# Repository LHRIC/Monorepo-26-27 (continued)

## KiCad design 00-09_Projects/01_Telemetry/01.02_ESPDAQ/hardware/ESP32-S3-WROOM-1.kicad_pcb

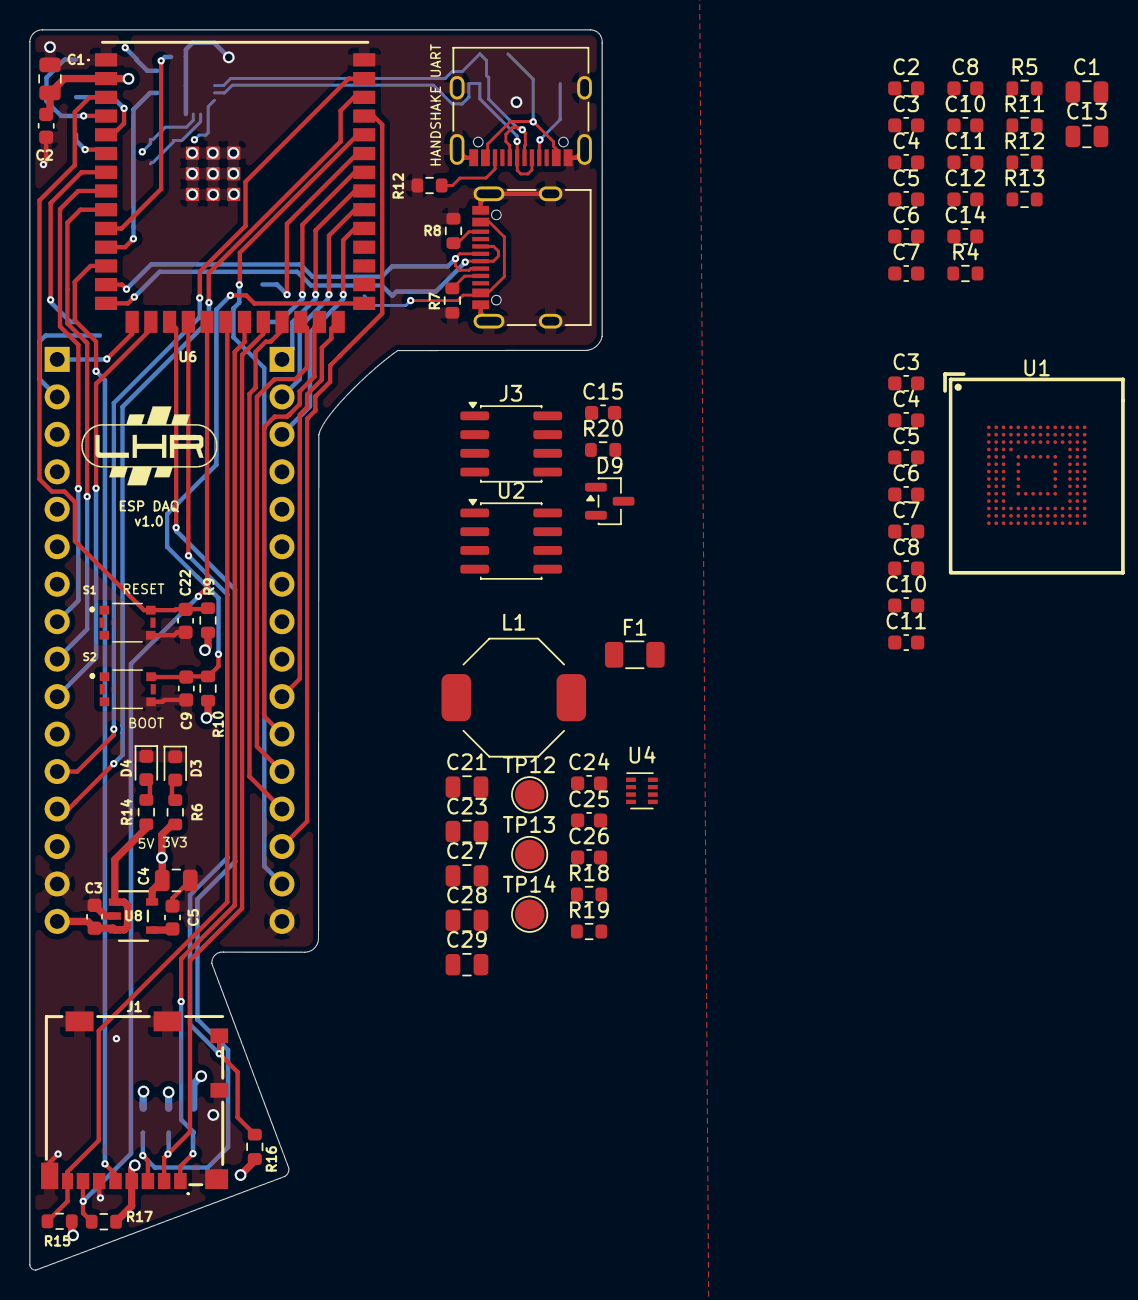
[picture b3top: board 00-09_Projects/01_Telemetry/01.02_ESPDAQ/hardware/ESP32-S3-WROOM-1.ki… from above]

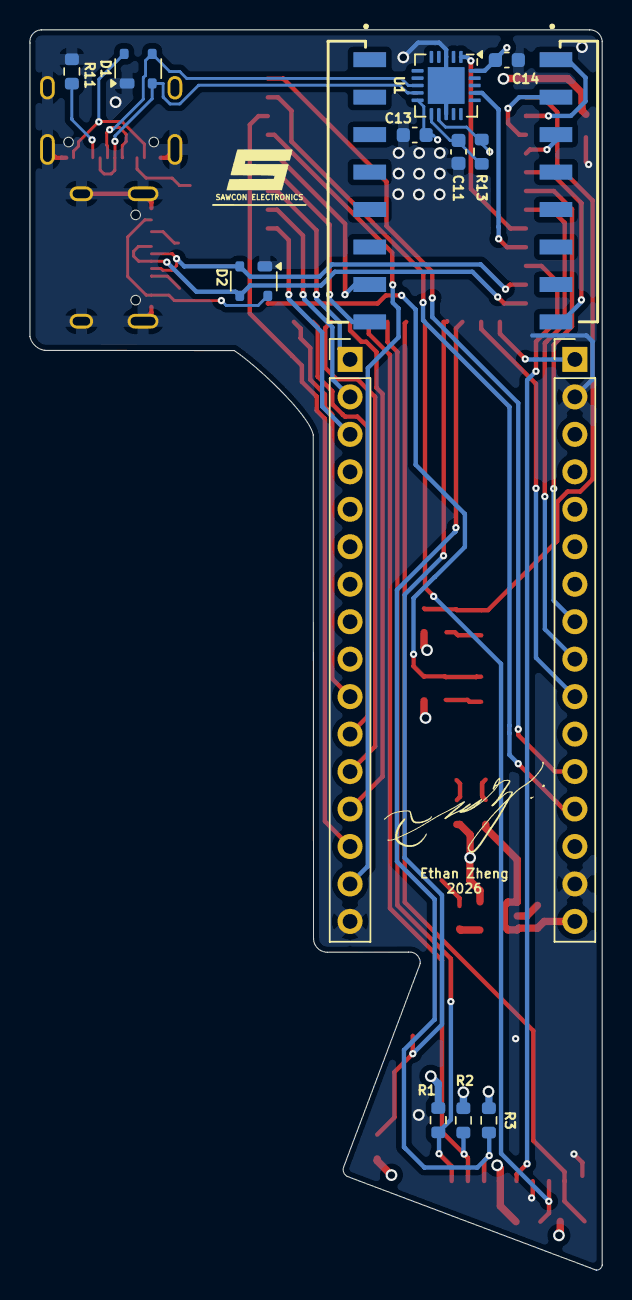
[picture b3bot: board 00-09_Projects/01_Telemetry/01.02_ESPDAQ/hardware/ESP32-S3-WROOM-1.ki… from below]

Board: 4 copper layers, 38.8 x 84.1 mm, 89 parts (15 on the bottom side), 42 nets.

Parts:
C1, C1#2, C13, C27, C28, C29: 22uF; C_0805_2012Metric
C2, C2#2, C3, C3#3, C4#2, C4#3, C5#2, C5#3, C6, C6#2, C7, C7#2, C8, C8#2, C9, C10, C10#2, C11, C11#2, C11#3, C12, C13#2, C14, C14#2, C15: 0.1uF; C_0603_1608Metric
C3#2: .47uF; C_0603_1608Metric
C4: 33uF; C_0805_2012Metric
C5: 100pF; C_0603_1608Metric
C21, C23: 4.7uF; C_0805_2012Metric
C22: 1uF; C_0603_1608Metric
C24, C26: .1uF; C_0603_1608Metric
C25: 33nF; C_0603_1608Metric
D1, D2: PRTR5V0U2X; SOT-143
D3, D4: RED; LED_0603_1608Metric
D9: D_TVS_Dual_AAC; SOT-23
F1: Fuse; Fuse_1206_3216Metric
J1: 104031-0811; Molex MicroSD Card 1040310811
J3: Conn_02x03_Counter_Clockwise; SOIC-8_3.9x4.9mm_P1.27mm
J9, J10: USB_C_Receptacle_USB2.0_14P; USB_C_Receptacle_XKB_U262-16XN-4BVC11
J12, J14: Conn_01x16; PinHeader_1x16_P2.54mm_Vertical
J15: Conn_01x08; 01x08 2.54mm Connector Surface Mount Right Angle Left
J16: Conn_01x08; 01x08 2.54mm Connector Surface Mount Right Angle Right
L1: 4.7uH; SRU8043-4R7Y
R1, R2, R3, R4, R5, R9, R10, R11, R12#2, R13, R15, R16, R17, R19: 10k; R_0603_1608Metric
R6, R14: 330; R_0603_1608Metric
R7, R8, R11#2, R12, R13#2: 5.1k; R_0603_1608Metric
R18: 30.9k; R_0603_1608Metric
R20: 120; R_0603_1608Metric
S1, S2: 435171014816; SMT Switch 435171014816
TP12, TP13, TP14: TP; TestPoint_Pad_D2.0mm
U1: KLMAG1JETD-B041; FBGA-153_L13.0-W11.5-P0.50_KLMAG1JETD-B041
U1#2: FT231XQ; QFN-20-1EP_4x4mm_P0.5mm_EP2.5x2.5mm
U2: SN65HVD230; SOIC-8_3.9x4.9mm_P1.27mm
U4: TPS62933; SOT-583
U6: ESP32-S3-WROOM-1; ESP32S3-WROOM-1U-N16R8
U8: AP2210K-3.3TRG1; SOT-23-5_DIO

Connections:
+3V3: C1.1, C1#2.1, C2.1, C2#2.1, C3.1, C3#3.1, C4.2, C4#2.1, C4#3.1, C5#2.1, C5#3.1, C6.1, C6#2.1, C7.1, C7#2.1, C8.1, C8#2.1, C10.1, C10#2.1, C11.1, C11#2.1, C12.1, C13.1, C13#2.1, C14.1, C14#2.2, C15.1, F1.2, J1.4 (VDD), R1.1, R2.1, R3.1, R4.1, R5.1, R6.1, R9.1, R10.1, R11.1, R12#2.1, R13.1, R13#2.2, R15.1, R16.1, R17.1, U1.C2 (VDDI), U1.C6 (VDD), U1.E6 (VDDF), U1.F5 (VDDF), U1.J10 (VDDF), U1.K9 (VDDF), U1.M4 (VDD), U1.N4 (VDD), U1.P3 (VDD), U1.P5 (VDD), U1#2.10 (3V3OUT), U1#2.12 (VCC), U1#2.20 (VCCIO), U2.3 (VCC), U6.2 (3V3), U8.5 (VOUT)
+5V: C3#2.2, C21.1, C23.1, C24.1, J3.1, J12.16, R14.1, TP12.1 (1_1), U4.3 (VIN), U8.1 (VIN), U8.3 (EN)
/BOOT: C9.2, R10.2, S2.2, U6.27 (IO0)
/RESET: C22.2, R9.2, S1.2, U6.3 (EN)
CAN_H: D9.2 (A2), J3.6, R20.1, U2.7 (CANH)
CAN_L: D9.1 (A1), J3.5, R20.2, U2.6 (CANL)
CAN_RX: J12.13, U2.4 (R), U6.38 (IO2)
CAN_TX: J12.12, U2.1 (D), U6.39 (IO1)
Data_Log: J3.4, J14.13, U6.23 (IO21)
GND: C1.2, C1#2.2, C2.2, C2#2.2, C3.2, C3#2.1, C3#3.2, C4.1, C4#2.2, C4#3.2, C5.1, C5#2.2, C5#3.2, C6.2, C6#2.2, C7.2, C7#2.2, C8.2, C8#2.2, C9.1, C10.2, C10#2.2, C11.2, C11#2.2, C11#3.2, C12.2, C13.2, C13#2.2, C14.2, C14#2.1, C15.2, C21.2, C22.1, C23.2, C24.2, C25.2, C27.2, C28.2, C29.2, D1.1 (GND), D2.1 (GND), D3.1 (K), D4.1 (K), D9.3 (common), J1.6 (VSS), J1.9, J1.10, J1.11, J1.13, J1.14, J3.3, J9.A1 (GND), J9.A12 (GND), J9.B1 (GND), J9.B12 (GND), J9.S1 (SHIELD), J10.A1 (GND), J10.A12 (GND), J10.B1 (GND), J10.B12 (GND), J10.S1 (SHIELD), J12.2, J12.15, J14.16, R7.2, R8.2, R11#2.2, R12.2, R19.2, S1.4, S1.6, S2.4, S2.6, TP13.1 (1_1), U1.A6 (VSS), U1.C4 (VSS), U1.E7 (VSS), U1.G5 (VSS), U1.H10 (VSS), U1.J5 (VSS), U1.K8 (VSS), U1.N2 (VSS), U1.N5 (VSS), U1.P4 (VSS), U1.P6 (VSS), U1#2.3 (GND), U1#2.13 (GND), U1#2.21 (GND), U2.2 (GND), U4.4 (GND), U6.1 (GND), U6.40 (GND), U6.41 (GND), U8.2 (GND)
MMC_CLK: U1.M6 (CLK), U6.35 (IO42)
MMC_CMD: R13.2, U1.M5 (CMD), U6.24 (IO47)
MMC_D0: R4.2, U1.A3 (DAT0), U6.31 (IO38)
MMC_D1: R5.2, U1.A4 (DAT1), U6.32 (IO39)
MMC_D2: R11.2, U1.A5 (DAT2), U6.33 (IO40)
MMC_D3: R12#2.2, U1.B2 (DAT3), U6.34 (IO41)
unnamed: C27.1, C28.1, C29.1, F1.1, L1.2, R18.1, TP14.1 (1_1)
unnamed: D1.4 (VCC), J10.A4 (VBUS), J10.A9 (VBUS), J10.B4 (VBUS), J10.B9 (VBUS)
unnamed: D2.4 (VCC), J9.A4 (VBUS), J9.A9 (VBUS), J9.B4 (VBUS), J9.B9 (VBUS)
unnamed: D3.2 (A), R6.2
unnamed: D4.2 (A), R14.2
unnamed: J9.A5 (CC1), R7.1
unnamed: J9.B5 (CC2), R8.1
unnamed: J10.A5 (CC1), R11#2.1
unnamed: J10.B5 (CC2), R12.1
unnamed: C11#3.1, R13#2.1, U1#2.11 (~RESET)
unnamed: C26.2, U4.6 (BST)
unnamed: R18.2, R19.1, U4.8 (FB)
unnamed: C25.1, U4.7 (SS)
unnamed: C26.1, L1.1, U4.5 (SW)
unnamed: C5.2, U8.4 (BYP/ADJ)
SD_CLK: J1.5 (CLK), U6.12 (IO8)
SD_CMD: J1.3 (CMD), R3.2, U6.17 (IO9)
SD_D0: J1.7 (DAT0), R17.2, U6.19 (IO11)
SD_D1: J1.8 (DAT1), R15.2, U6.20 (IO12)
SD_D2: J1.1 (DAT2), R1.2, U6.21 (IO13)
SD_D3: J1.2 (CD/DAT3), R2.2, U6.22 (IO14)
SD_DET: J1.12, R16.2, U6.18 (IO10)
U0D+: D1.3 (I/O2), J10.A6 (D+), J10.B6 (D+), U1#2.8 (USBDP)
U0D-: D1.2 (I/O1), J10.A7 (D-), J10.B7 (D-), U1#2.9 (USBDM)
USB_D+: D2.3 (I/O2), J9.A6 (D+), J9.B6 (D+), U6.14 (USB_D+)
USB_D-: D2.2 (I/O1), J9.A7 (D-), J9.B7 (D-), U6.13 (USB_D-)

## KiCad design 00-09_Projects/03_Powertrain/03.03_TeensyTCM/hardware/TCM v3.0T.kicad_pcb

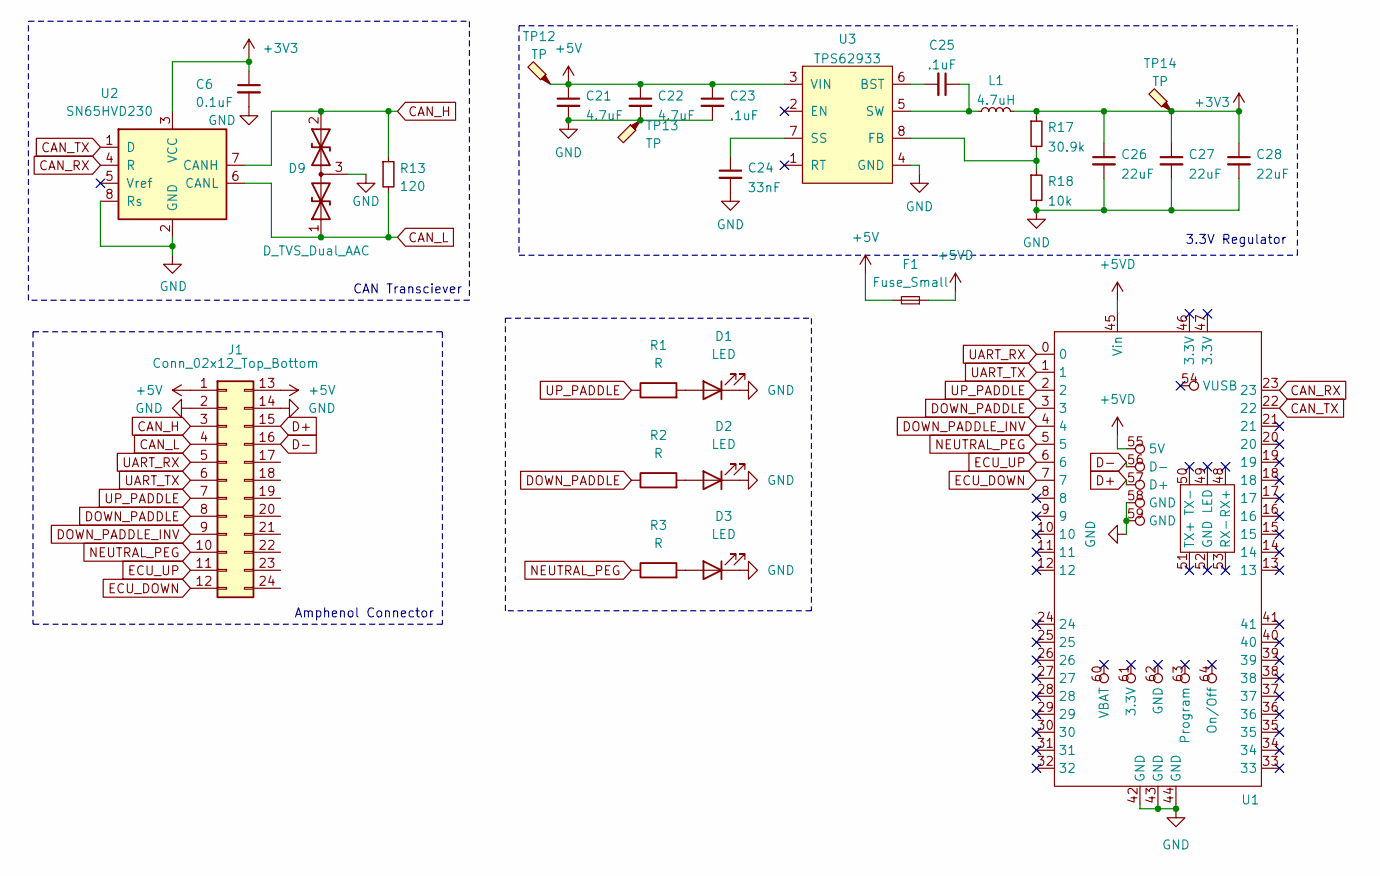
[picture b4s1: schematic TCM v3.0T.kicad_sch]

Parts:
C6: 0.1uF; C_0603_1608Metric
C21, C22: 4.7uF; C_0805_2012Metric
C23, C25: .1uF; C_0603_1608Metric
C24: 33nF; C_0603_1608Metric
C26, C27, C28: 22uF; C_0805_2012Metric
D1, D2, D3: LED; LED_0201_0603Metric
D9: D_TVS_Dual_AAC; SOT-23
F1: Fuse_Small; Fuse_1206_3216Metric
J1: Conn_02x12_Top_Bottom; AMPHENOL_PCB_24P
L1: 4.7uH; SRU8043-4R7Y
R1, R2, R3: R; R_0603_1608Metric_Pad0.98x0.95mm_HandSolder
R13: 120; R_0603_1608Metric
R17: 30.9k; R_0603_1608Metric
R18: 10k; R_0603_1608Metric
TP12, TP13, TP14: TP; TestPoint_Pad_D2.0mm
U1: Teensy 4.1
U2: SN65HVD230; SOIC-8_3.9x4.9mm_P1.27mm
U3: TPS62933; SOT-583

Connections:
+3V3: C6.1, C26.1, C27.1, C28.1, L1.2, R17.1, TP14.1, U2.3 (VCC)
+5V: C21.1, C22.1, C23.1, F1.2, J1.1, J1.13, TP12.1, U3.3 (VIN)
+5VD: F1.1, U1.45 (Vin), U1.55 (5V)
CAN_H: D9.2 (A2), J1.3, R13.1, U2.7 (CANH)
CAN_L: D9.1 (A1), J1.4, R13.2, U2.6 (CANL)
CAN_RX: U1.23, U2.4 (R)
CAN_TX: U1.22, U2.1 (D)
D+: J1.15, U1.57 (D+)
D-: J1.16, U1.56 (D-)
DOWN_PADDLE: J1.8, R2.1, U1.3
DOWN_PADDLE_INV: J1.9, U1.4
ECU_DOWN: J1.12, U1.7
ECU_UP: J1.11, U1.6
GND: C6.2, C21.2, C22.2, C23.2, C24.2, C26.2, C27.2, C28.2, D1.1 (K), D2.1 (K), D3.1 (K), D9.3 (common), J1.2, J1.14, R18.2, TP13.1, U1.42 (GND), U1.43 (GND), U1.44 (GND), U1.58 (GND), U1.59 (GND), U2.2 (GND), U2.8 (Rs), U3.4 (GND)
NEUTRAL_PEG: J1.10, R3.1, U1.5
unnamed: D1.2 (A), R1.2
unnamed: D2.2 (A), R2.2
unnamed: D3.2 (A), R3.2
unnamed: C25.2, U3.6 (BST)
unnamed: R17.2, R18.1, U3.8 (FB)
unnamed: C24.1, U3.7 (SS)
unnamed: C25.1, L1.1, U3.5 (SW)
UART_RX: J1.5, U1.0
UART_TX: J1.6, U1.1
UP_PADDLE: J1.7, R1.1, U1.2

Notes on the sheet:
3.3V Regulator
Amphenol Connector
CAN Transciever

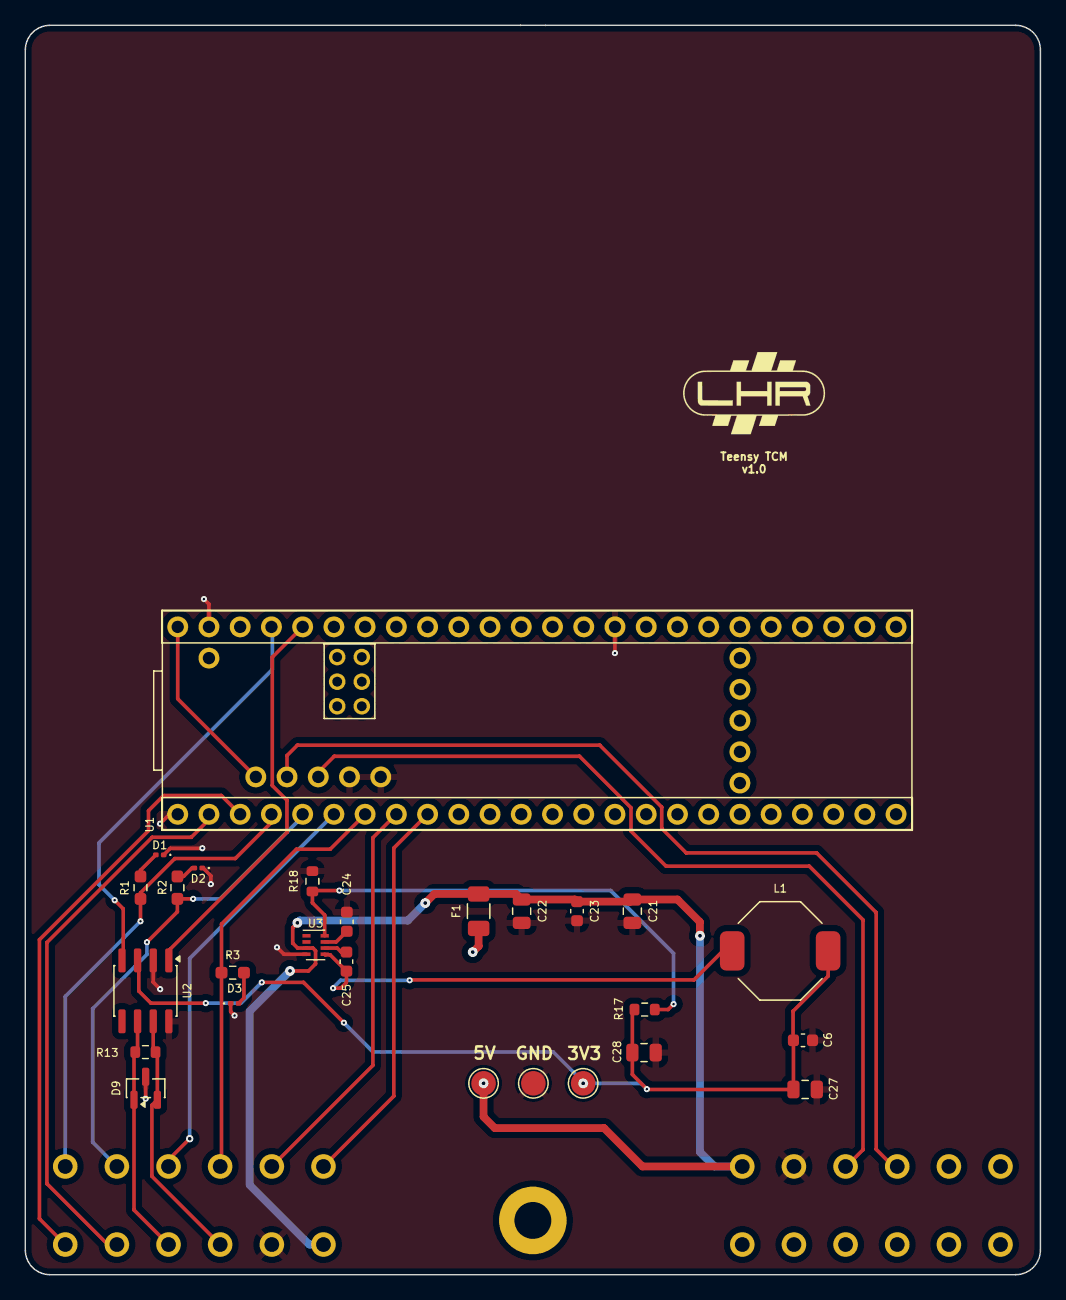
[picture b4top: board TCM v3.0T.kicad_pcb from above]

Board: 4 copper layers, 82.5 x 101.6 mm, 27 parts (0 on the bottom side), 25 nets.

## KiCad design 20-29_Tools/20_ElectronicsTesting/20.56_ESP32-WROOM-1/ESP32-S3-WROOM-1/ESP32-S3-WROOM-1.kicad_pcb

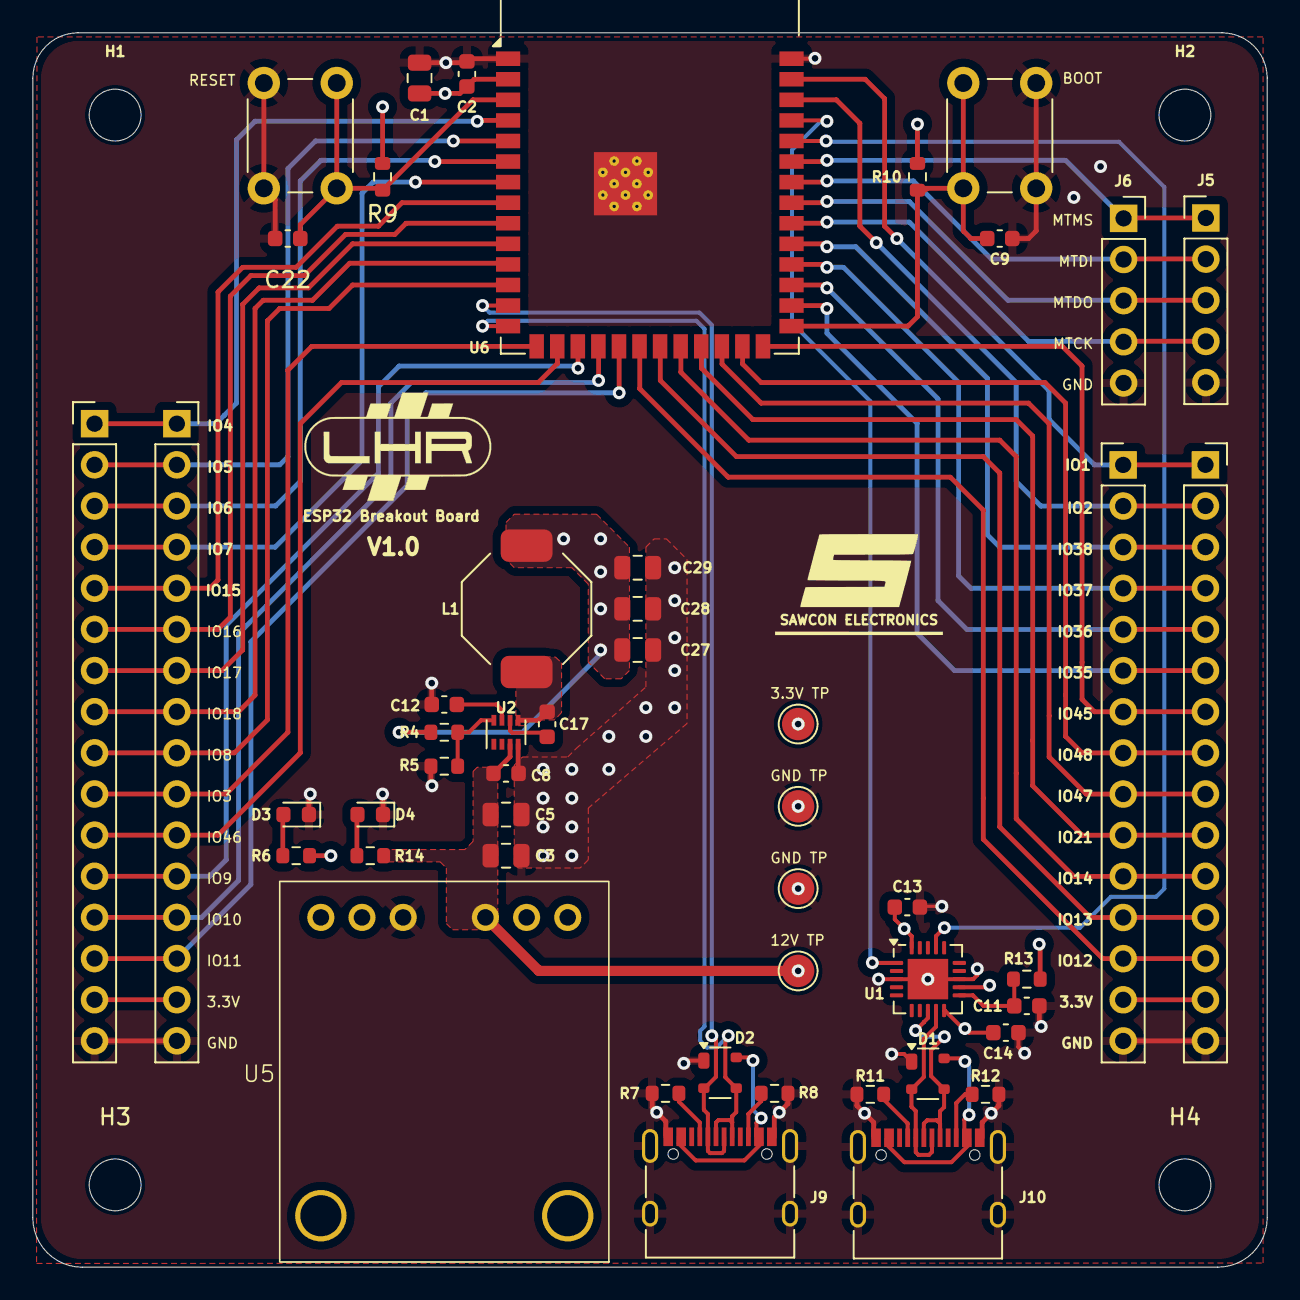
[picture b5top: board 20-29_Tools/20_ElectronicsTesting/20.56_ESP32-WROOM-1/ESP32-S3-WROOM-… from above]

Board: 4 copper layers, 76.2 x 76.2 mm, 53 parts (0 on the bottom side), 55 nets.

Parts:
C1, C27, C28, C29: 22uF; C_0805_2012Metric
C2, C8, C9, C11, C13, C14, C17: 0.1uF; C_0603_1608Metric
C3, C5: 4.7uF; C_0805_2012Metric
C12: 33nF; C_0603_1608Metric
C22: 1uF; C_0603_1608Metric
D1, D2: PRTR5V0U2X; SOT-143
D3, D4: RED; LED_0603_1608Metric
H1, H2, H3, H4: MountingHole; MountingHole_3.2mm_M3
J1: Conn_01x16; PinHeader_1x16_P2.54mm_Vertical
J2: Conn_01x16; PinSocket_1x16_P2.54mm_Vertical
J3: Conn_01x15; PinHeader_1x15_P2.54mm_Vertical
J4: Conn_01x15; PinSocket_1x15_P2.54mm_Vertical
J5: Conn_01x05; PinHeader_1x05_P2.54mm_Vertical
J6: Conn_01x05; PinSocket_1x05_P2.54mm_Vertical
J9, J10: USB_C_Receptacle_USB2.0_14P; USB_C_Receptacle_XKB_U262-16XN-4BVC11
L1: 4.7uH; SRU8043-4R7Y
R4: 30.9k; R_0603_1608Metric
R5, R9, R10: 10k; R_0603_1608Metric
R6: 330; R_0603_1608Metric
R7, R8, R11, R12, R13, R14: 5.1k; R_0603_1608Metric
SW1, SW2: SW_Push; SW_PUSH_6mm
TP1, TP2, TP5, TP6: TP; TestPoint_Pad_D2.0mm
U1: FT231XQ; QFN-20-1EP_4x4mm_P0.5mm_EP2.5x2.5mm
U2: TPS62933; SOT-583
U5: Adafruit HUSB238 USB PD
U6: ESP32-S3-WROOM-1

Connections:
+3V3: C1.1, C2.1, C13.1, C14.2, C27.1, C28.1, C29.1, J1.15, J2.15, J3.14, J4.14, L1.2, R4.1, R6.1, R9.1, R10.1, R13.2, TP5.1, U1.10 (3V3OUT), U1.12 (VCC), U1.20 (VCCIO), U6.2 (3V3)
+12V: C3.1, C5.1, C8.1, R14.1, TP1.1, U2.3 (VIN), U5.4
/BOOT: C9.2, R10.2, SW1.2, U6.27 (IO0)
/RESET: C22.2, R9.2, SW2.2, U6.3 (EN)
GND: C1.2, C2.2, C3.2, C5.2, C8.2, C9.1, C11.2, C12.2, C13.2, C14.1, C22.1, C27.2, C28.2, C29.2, D1.1 (GND), D2.1 (GND), D3.1 (K), D4.1 (K), J1.16, J2.16, J3.15, J4.15, J5.5, J6.5, J9.A1 (GND), J9.A12 (GND), J9.B1 (GND), J9.B12 (GND), J9.S1 (SHIELD), J10.A1 (GND), J10.A12 (GND), J10.B1 (GND), J10.B12 (GND), J10.S1 (SHIELD), R5.2, R7.2, R8.2, R11.2, R12.2, SW1.1, SW2.1, TP2.1, TP6.1, U1.3 (GND), U1.13 (GND), U1.21 (GND), U2.4 (GND), U5.3, U6.1 (GND), U6.40 (GND), U6.41 (GND)
GPIO1: J3.1, J4.1, U6.39 (IO1)
GPIO2: J3.2, J4.2, U6.38 (IO2)
GPIO3: J1.10, J2.10, U6.15 (IO3)
GPIO4: J1.1, J2.1, U6.4 (IO4)
GPIO5: J1.2, J2.2, U6.5 (IO5)
GPIO6: J1.3, J2.3, U6.6 (IO6)
GPIO7: J1.4, J2.4, U6.7 (IO7)
GPIO8: J1.9, J2.9, U6.12 (IO8)
GPIO9: J1.12, J2.12, U6.17 (IO9)
GPIO10: J1.13, J2.13, U6.18 (IO10)
GPIO11: J1.14, J2.14, U6.19 (IO11)
GPIO12: J3.13, J4.13, U6.20 (IO12)
GPIO13: J3.12, J4.12, U6.21 (IO13)
GPIO14: J3.11, J4.11, U6.22 (IO14)
GPIO15: J1.5, J2.5, U6.8 (IO15)
GPIO16: J1.6, J2.6, U6.9 (IO16)
GPIO17: J1.7, J2.7, U6.10 (IO17)
GPIO18: J1.8, J2.8, U6.11 (IO18)
GPIO21: J3.10, J4.10, U6.23 (IO21)
GPIO35: J3.6, J4.6, U6.28 (IO35)
GPIO36: J3.5, J4.5, U6.29 (IO36)
GPIO37: J3.4, J4.4, U6.30 (IO37)
GPIO38: J3.3, J4.3, U6.31 (IO38)
GPIO45: J3.7, J4.7, U6.26 (IO45)
GPIO46: J1.11, J2.11, U6.16 (IO46)
GPIO47: J3.9, J4.9, U6.24 (IO47)
GPIO48: J3.8, J4.8, U6.25 (IO48)
MTCK: J5.4, J6.4, U6.32 (IO39)
MTDI: J5.2, J6.2, U6.34 (IO41)
MTDO: J5.3, J6.3, U6.33 (IO40)
MTMS: J5.1, J6.1, U6.35 (IO42)
unnamed: D1.4 (VCC), J10.A4 (VBUS), J10.A9 (VBUS), J10.B4 (VBUS), J10.B9 (VBUS)
unnamed: D2.4 (VCC), J9.A4 (VBUS), J9.A9 (VBUS), J9.B4 (VBUS), J9.B9 (VBUS)
unnamed: D3.2 (A), R6.2
unnamed: D4.2 (A), R14.2
unnamed: J9.A5 (CC1), R7.1
unnamed: J9.B5 (CC2), R8.1
unnamed: J10.A5 (CC1), R11.1
unnamed: J10.B5 (CC2), R12.1
unnamed: C11.1, R13.1, U1.11 (~RESET)
unnamed: C17.2, U2.6 (BST)
unnamed: R4.2, R5.1, U2.8 (FB)
unnamed: C12.1, U2.7 (SS)
unnamed: C17.1, L1.1, U2.5 (SW)
RXD0: U1.17 (TXD), U6.36 (RXD0)
TXD0: U1.1 (RXD), U6.37 (TXD0)
U0D+: D1.3 (I/O2), J10.A6 (D+), J10.B6 (D+), U1.8 (USBDP)
U0D-: D1.2 (I/O1), J10.A7 (D-), J10.B7 (D-), U1.9 (USBDM)
USB_D+: D2.3 (I/O2), J9.A6 (D+), J9.B6 (D+), U6.14 (USB_D+)
USB_D-: D2.2 (I/O1), J9.A7 (D-), J9.B7 (D-), U6.13 (USB_D-)

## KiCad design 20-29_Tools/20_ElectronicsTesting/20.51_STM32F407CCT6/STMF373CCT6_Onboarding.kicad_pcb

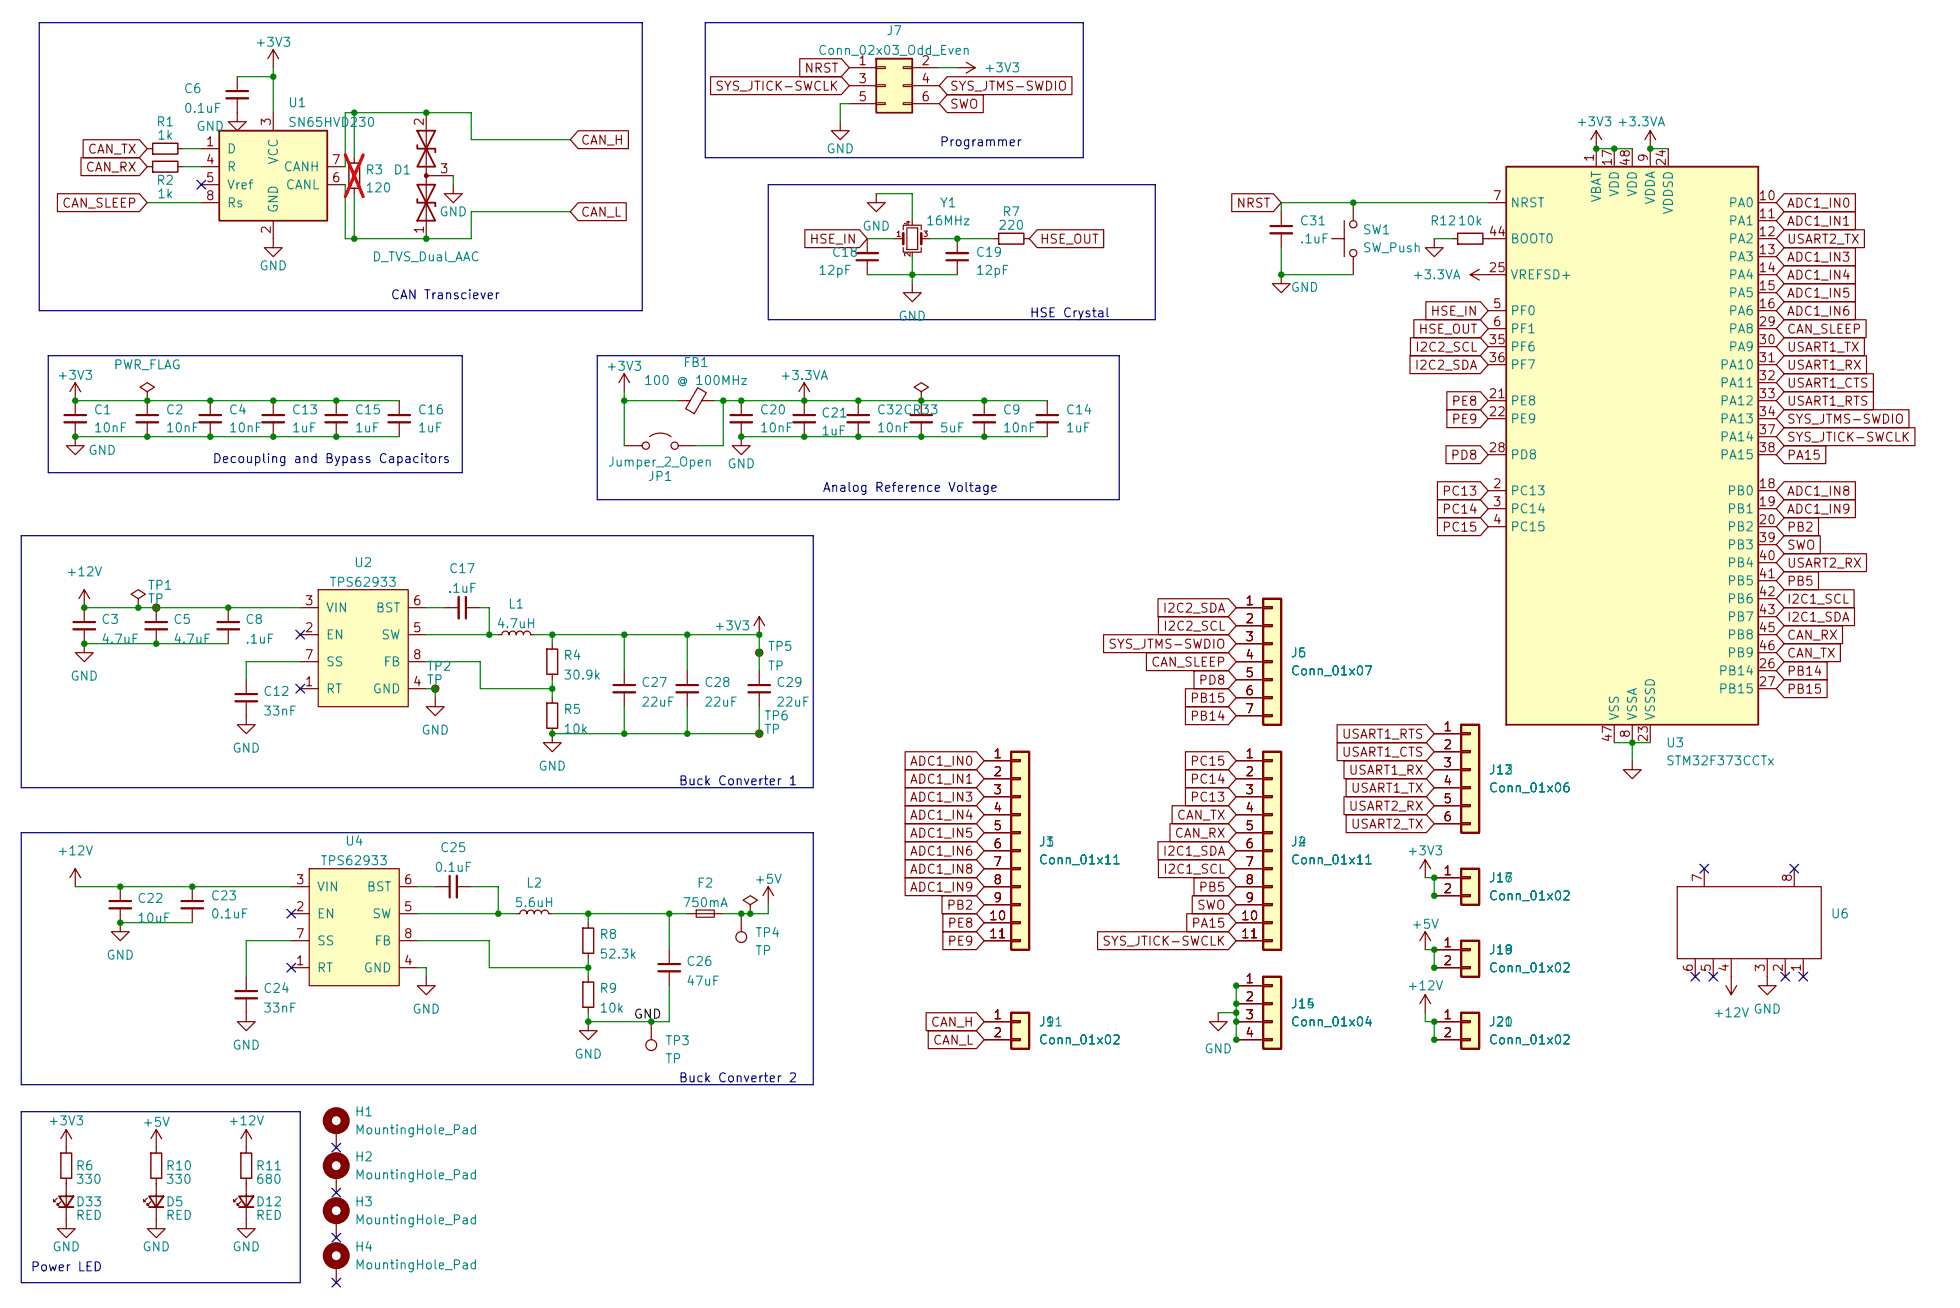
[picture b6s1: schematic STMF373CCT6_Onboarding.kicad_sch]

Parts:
C1, C2, C4, C9, C20, C32: 10nF; C_0603_1608Metric
C3, C5: 4.7uF; C_0805_2012Metric
C6, C23, C25: 0.1uF; C_0603_1608Metric
C8, C17, C31: .1uF; C_0603_1608Metric
C12, C24: 33nF; C_0603_1608Metric
C13, C14, C15, C16, C21: 1uF; C_0603_1608Metric
C18, C19: 12pF; C_0402_1005Metric
C22: 10uF; C_0603_1608Metric
C26: 47uF; C_0603_1608Metric
C27, C28, C29: 22uF; C_0805_2012Metric
CR33: 5uF; C_0603_1608Metric
D1: D_TVS_Dual_AAC; SOT-23
D5, D12, D33: RED; LED_0603_1608Metric
F2: 750mA; Fuse_1206_3216Metric
FB1: 100 @ 100MHz; C_0402_1005Metric
H1, H2, H3, H4: MountingHole_Pad; MountingHole_3.2mm_M3_DIN965_Pad
J1, J2, J3, J4: Conn_01x11; PinHeader_1x11_P2.54mm_Vertical
J5, J6: Conn_01x07; PinHeader_1x07_P2.54mm_Vertical
J7: Conn_02x03_Odd_Even; Molex_Micro-Fit_3.0_43045-0612_2x03_P3.00mm_Vertical
J9, J11, J16, J17, J18, J19, J20, J21: Conn_01x02; PinHeader_1x02_P2.54mm_Vertical
J12, J13: Conn_01x06; PinHeader_1x06_P2.54mm_Vertical
J14, J15: Conn_01x04; PinHeader_1x04_P2.54mm_Vertical
JP1: Jumper_2_Open; SolderJumper-2_P1.3mm_Open_RoundedPad1.0x1.5mm
L1: 4.7uH; SRU8043-4R7Y
L2: 5.6uH; HCMA1305-5R6-R
R1, R2: 1k; R_0603_1608Metric
R3: 120; R_0603_1608Metric; not fitted
R4: 30.9k; R_0603_1608Metric
R5, R9, R12: 10k; R_0603_1608Metric
R6, R10: 330; R_0603_1608Metric
R7: 220; R_0603_1608Metric
R8: 52.3k; R_0603_1608Metric
R11: 680; R_0603_1608Metric
SW1: SW_Push; SW_PUSH_6mm
TP1, TP2, TP3, TP4, TP5, TP6: TP; TestPoint_Pad_D2.0mm
U1: SN65HVD230; SOIC-8_3.9x4.9mm_P1.27mm
U2, U4: TPS62933; SOT-583
U3: STM32F373CCTx; LQFP-48_7x7mm_P0.5mm
U6: Adafruit HUSB238 USB PD
Y1: 16MHz; Crystal_SMD_3225-4Pin_3.2x2.5mm

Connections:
+3.3VA: C9.1, C14.1, C20.1, C21.1, C32.1, CR33.1, FB1.2, JP1.2 (B), U3.9 (VDDA), U3.24 (VDDSD), U3.25 (VREFSD+); also elsewhere on the board
+3V3: C1.1, C2.1, C4.1, C6.1, C13.1, C15.1, C16.1, C27.1, C28.1, C29.1, FB1.1, J7.2, J16.1, J16.2, J17.1, J17.2, JP1.1 (A), L1.2, R4.1, R6.1, TP5.1, U1.3 (VCC), U3.1 (VBAT), U3.17 (VDD), U3.48 (VDD)
+5V: F2.2, J18.1, J18.2, J19.1, J19.2, R10.1, TP4.1
+12V: C3.1, C5.1, C8.1, C22.1, C23.1, J20.1, J20.2, J21.1, J21.2, R11.1, TP1.1, U2.3 (VIN), U4.3 (VIN), U6.4
ADC1_IN0: J1.1, J3.1, U3.10 (PA0)
ADC1_IN1: J1.2, J3.2, U3.11 (PA1)
ADC1_IN3: J1.3, J3.3, U3.13 (PA3)
ADC1_IN4: J1.4, J3.4, U3.14 (PA4)
ADC1_IN5: J1.5, J3.5, U3.15 (PA5)
ADC1_IN6: J1.6, J3.6, U3.16 (PA6)
ADC1_IN8: J1.7, J3.7, U3.18 (PB0)
ADC1_IN9: J1.8, J3.8, U3.19 (PB1)
CAN_H: D1.2 (A2), J9.1, J11.1, R3.1, U1.7 (CANH)
CAN_L: D1.1 (A1), J9.2, J11.2, R3.2, U1.6 (CANL)
CAN_RX: J2.5, J4.5, R2.1, U3.45 (PB8)
CAN_SLEEP: J5.4, J6.4, U1.8 (Rs), U3.29 (PA8)
CAN_TX: J2.4, J4.4, R1.1, U3.46 (PB9)
GND: C1.2, C2.2, C3.2, C4.2, C5.2, C6.2, C8.2, C9.2, C12.2, C13.2, C14.2, C15.2, C16.2, C18.1, C19.1, C20.2, C21.2, C22.2, C23.2, C24.2, C26.2, C27.2, C28.2, C29.2, C31.2, C32.2, CR33.2, D1.3 (common), D5.1 (K), D12.1 (K), D33.1 (K), J7.5, J14.1, J14.2, J14.3, J14.4, J15.1, J15.2, J15.3, J15.4, R5.2, R9.2, R12.1, SW1.1, TP2.1, TP3.1, TP6.1, U1.2 (GND), U2.4 (GND), U3.8 (VSSA), U3.23 (VSSSD), U3.47 (VSS), U4.4 (GND), U6.3, Y1.2, Y1.4; also elsewhere on the board
HSE_IN: C18.2, U3.5 (PF0), Y1.1
HSE_OUT: R7.2, U3.6 (PF1)
I2C1_SCL: J2.7, J4.7, U3.42 (PB6)
I2C1_SDA: J2.6, J4.6, U3.43 (PB7)
I2C2_SCL: J5.2, J6.2, U3.35 (PF6)
I2C2_SDA: J5.1, J6.1, U3.36 (PF7)
NRST: C31.1, J7.1, SW1.2, U3.7 (NRST)
unnamed: C19.2, R7.1, Y1.3
unnamed: C26.1, F2.1, L2.2, R8.1
unnamed: D5.2 (A), R10.2
unnamed: D12.2 (A), R11.2
unnamed: D33.2 (A), R6.2
unnamed: R1.2, U1.1 (D)
unnamed: R2.2, U1.4 (R)
unnamed: C17.2, U2.6 (BST)
unnamed: R4.2, R5.1, U2.8 (FB)
unnamed: C12.1, U2.7 (SS)
unnamed: C17.1, L1.1, U2.5 (SW)
unnamed: R12.2, U3.44 (BOOT0)
unnamed: C25.1, U4.6 (BST)
unnamed: R8.2, R9.1, U4.8 (FB)
unnamed: C24.1, U4.7 (SS)
unnamed: C25.2, L2.1, U4.5 (SW)
PA15: J2.10, J4.10, U3.38 (PA15)
PB2: J1.9, J3.9, U3.20 (PB2)
PB5: J2.8, J4.8, U3.41 (PB5)
PB14: J5.7, J6.7, U3.26 (PB14)
PB15: J5.6, J6.6, U3.27 (PB15)
PC13: J2.3, J4.3, U3.2 (PC13)
PC14: J2.2, J4.2, U3.3 (PC14)
PC15: J2.1, J4.1, U3.4 (PC15)
PD8: J5.5, J6.5, U3.28 (PD8)
PE8: J1.10, J3.10, U3.21 (PE8)
PE9: J1.11, J3.11, U3.22 (PE9)
SWO: J2.9, J4.9, J7.6, U3.39 (PB3)
SYS_JTICK-SWCLK: J2.11, J4.11, J7.3, U3.37 (PA14)
SYS_JTMS-SWDIO: J5.3, J6.3, J7.4, U3.34 (PA13)
USART1_CTS: J12.2, J13.2, U3.32 (PA11)
USART1_RTS: J12.1, J13.1, U3.33 (PA12)
USART1_RX: J12.3, J13.3, U3.31 (PA10)
USART1_TX: J12.4, J13.4, U3.30 (PA9)
USART2_RX: J12.5, J13.5, U3.40 (PB4)
USART2_TX: J12.6, J13.6, U3.12 (PA2)

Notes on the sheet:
Analog Reference Voltage
Decoupling and Bypass Capacitors
HSE Crystal
Programmer
Buck Converter 1
CAN Transciever
Buck Converter 2
Power LED

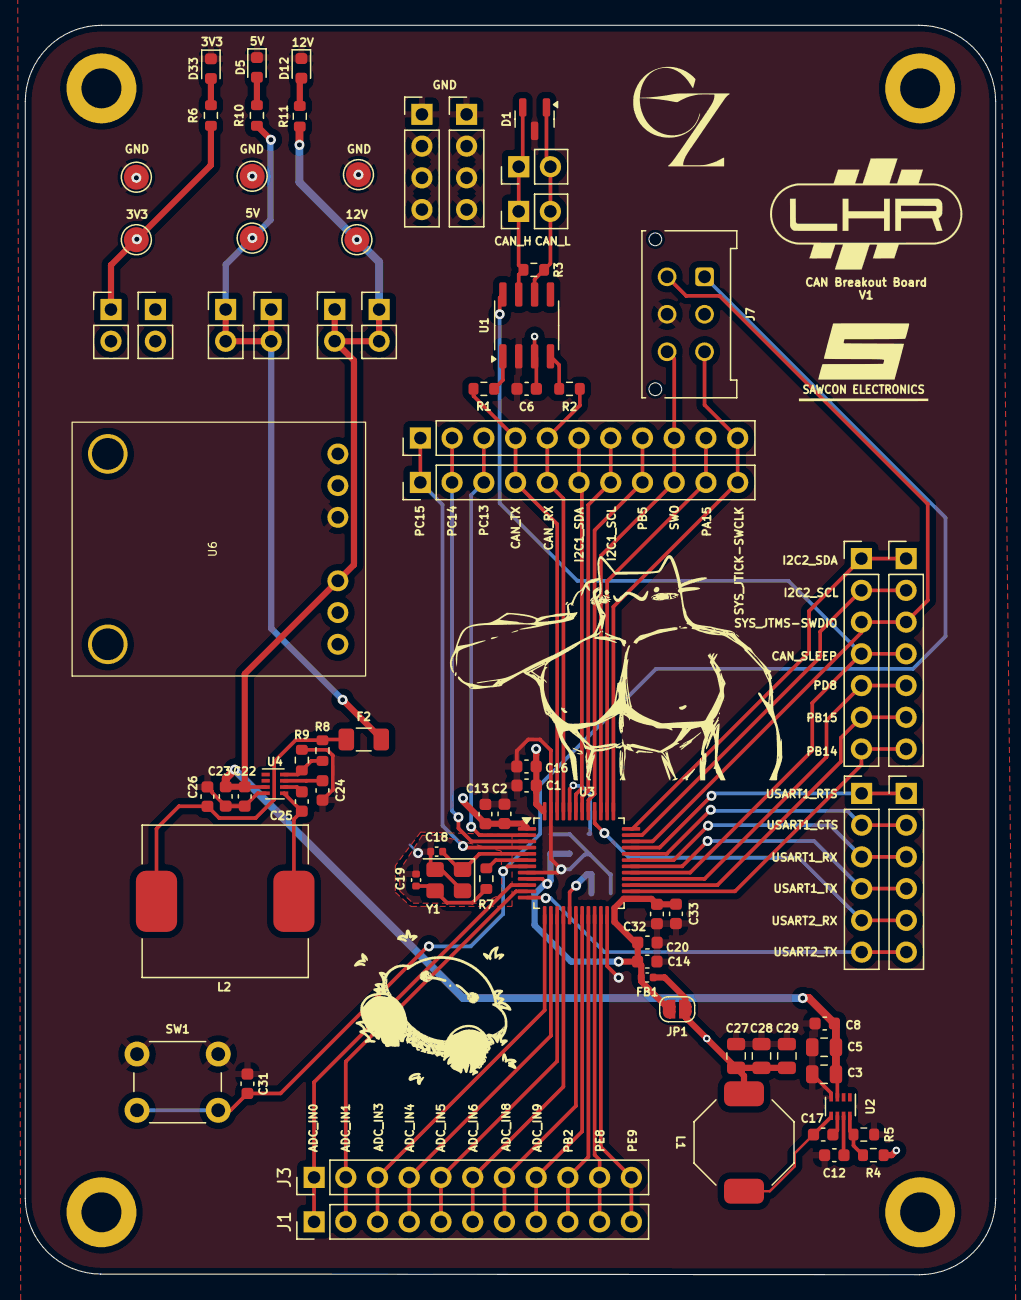
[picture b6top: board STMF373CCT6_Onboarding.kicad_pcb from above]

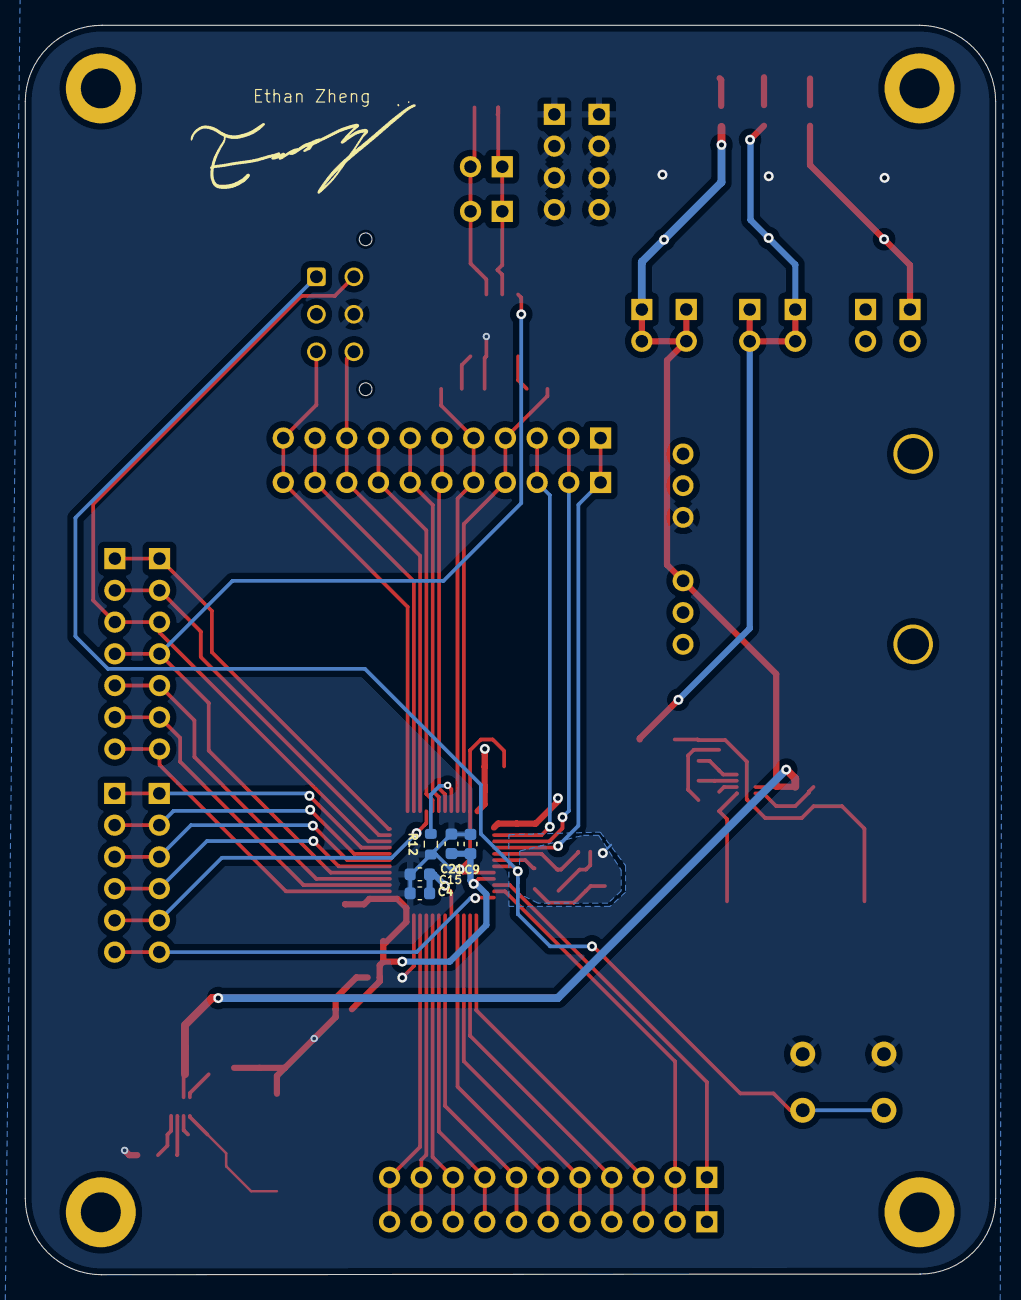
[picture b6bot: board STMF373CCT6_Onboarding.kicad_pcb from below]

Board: 4 copper layers, 77.7 x 100.0 mm, 86 parts (5 on the bottom side), 61 nets.

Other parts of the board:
C33: 5uF; C_0603_1608Metric

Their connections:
+3.3VA: C33.1; also elsewhere on the board
GND: C33.2; also elsewhere on the board

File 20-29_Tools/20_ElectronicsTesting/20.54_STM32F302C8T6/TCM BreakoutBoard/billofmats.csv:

"Reference","Value","Datasheet","Footprint","Qty","DNP"
"C1,C22","10uF","~","-- mixed values --","2",""
"C2,C4,C6,C7,C9,C10,C11,C14,C20,C23,C25","0.1uF","~","Capacitor_SMD:C_0603_1608Metric","11",""
"C3,C5","4.7uF","~","Capacitor_SMD:C_0805_2012Metric","2",""
"C8,C17",".1uF","~","Capacitor_SMD:C_0603_1608Metric","2",""
"C12,C24","33nF","~","Capacitor_SMD:C_0603_1608Metric","2",""
"C15,C16","100pF","~","Capacitor_SMD:C_0603_1608Metric","2",""
"C18,C19","12pF","~","Capacitor_SMD:C_0402_1005Metric","2",""
"C21","1uF","~","Capacitor_SMD:C_0603_1608Metric","1",""
"C26","47uF","~","Capacitor_SMD:C_0603_1608Metric","1",""
"C27,C28,C29","22uF","~","Capacitor_SMD:C_0805_2012Metric","3",""
"D1","D_TVS_Dual_AAC","~","Package_TO_SOT_SMD:SOT-23","1",""
"D2","RED","~","LED_SMD:LED_0603_1608Metric","1",""
"F2","750mA","~","Fuse:Fuse_1206_3216Metric","1",""
"FB1","100 @ 100MHz","~","Capacitor_SMD:C_0402_1005Metric","1",""
"J1,J2","Conn_01x03","~","-- mixed values --","2",""
"J3,J4","Conn_01x13","~","-- mixed values --","2",""
"J5,J6","Conn_01x12","~","-- mixed values --","2",""
"J7","Conn_02x03_Odd_Even","~","Connector_Molex:Molex_Micro-Fit_3.0_43045-0612_2x03_P3.00mm_Vertical","1",""
"J8,J9","Conn_01x10","~","-- mixed values --","2",""
"L1","4.7uH","~","LHR:SRU8043-4R7Y","1",""
"L2","5.6uH","~","LHR:HCMA1305-5R6-R","1",""
"R1,R2","1k","~","Resistor_SMD:R_0603_1608Metric","2",""
"R3","120","~","Resistor_SMD:R_0603_1608Metric","1",""
"R4","30.9k","~","Resistor_SMD:R_0603_1608Metric","1",""
"R5,R9","10k","~","Resistor_SMD:R_0603_1608Metric","2",""
"R6","330","~","Resistor_SMD:R_0603_1608Metric","1",""
"R7","220","~","Resistor_SMD:R_0603_1608Metric","1",""
"R8","52.3k","~","Resistor_SMD:R_0603_1608Metric","1",""
"TP1,TP2,TP3,TP4,TP5,TP6","TP","~","TestPoint:TestPoint_Pad_D2.0mm","6",""
"U1","SN65HVD230","http://www.ti.com/lit/ds/symlink/sn65hvd230.pdf","Package_SO:SOIC-8_3.9x4.9mm_P1.27mm","1",""
"U2,U4","TPS62933","","LHR:SOT-583","2",""
"U3","STM32F302C8Tx","https://www.st.com/resource/en/datasheet/stm32f302c8.pdf","Package_QFP:LQFP-48_7x7mm_P0.5mm","1",""
"U5","~","","LHR:Adafruit HUSB238 USB PD","1",""
"Y1","16MHz","~","Crystal:Crystal_SMD_3225-4Pin_3.2x2.5mm","1",""
